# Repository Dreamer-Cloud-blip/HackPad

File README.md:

# SixPad

A compact, custom-designed screwless 6-key mechanical macropad built with a Seeeduino XIAO, a rotary encoder, a 128x32 OLED display, and powered by Python-based KMK firmware.

## Overall Macropad

## Schematic

## PCB Design

## Case & Assembly

## Bill of Materials (BOM)

- **Seeeduino XIAO:** 1x microcontroller
- **Mechanical Switches:** 6x switches
- **Rotary Encoder:** 1x encoder
- **OLED Display:** 1x 128x32 display
- **Case Parts:** 3D-printed top plate and bottom tray

## Repository Directory Structure

```text
├── CAD/
│   └── assembly.step
├── PCB/
│   ├── SixPad.kicad_pro
│   ├── SixPad.kicad_sch
│   └── SixPad.kicad_pcb
├── Firmware/
│   └── main.py
├── production/
│   ├── Top.STEP
│   ├── Bottom.STEP
│   ├── gerbers.zip
│   └── main.py
└── assets/
    ├── CAD.png
    ├── Schematic.png
    ├── PCB_layout.png
    └── case_assembly.png

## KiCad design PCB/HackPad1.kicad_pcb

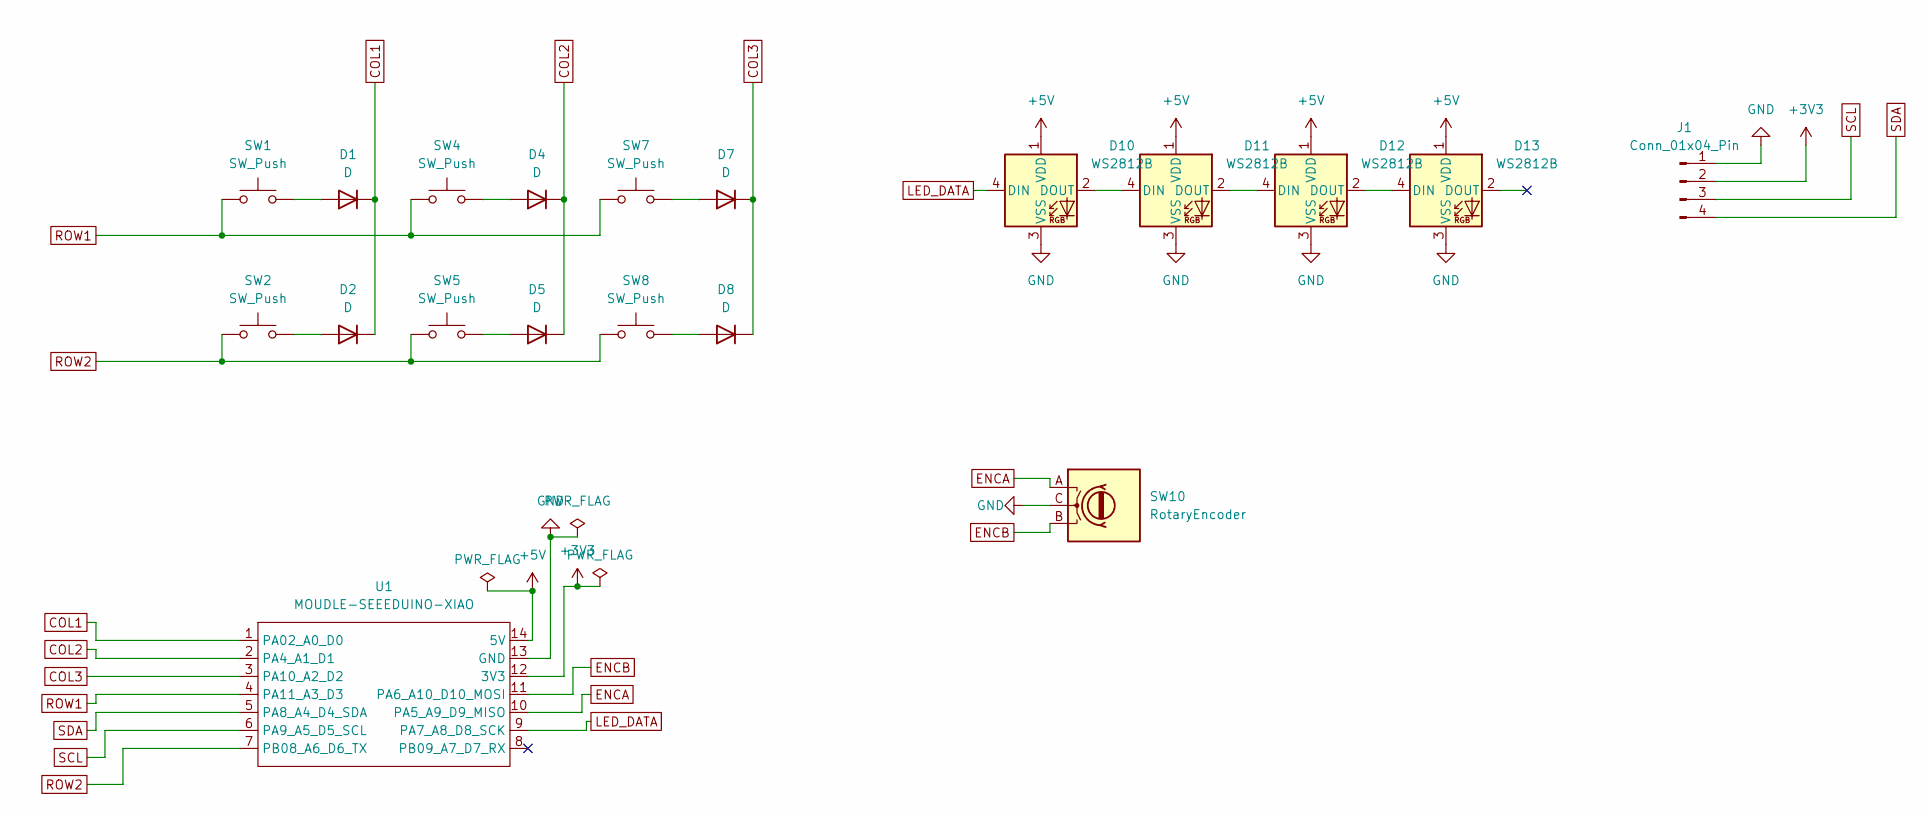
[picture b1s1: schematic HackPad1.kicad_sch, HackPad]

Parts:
D1, D2: D; D_DO-35_SOD27_P7.62mm_Horizontal
D4, D5, D7, D8: D; D_DO-35_SOD27_P10.16mm_Horizontal
D10, D11, D12, D13: WS2812B; LED_SK6812_PLCC4_5.0x5.0mm_P3.2mm
J1: Conn_01x04_Pin; PinSocket_1x04_P2.54mm_Vertical
SW1, SW2, SW4, SW5, SW7, SW8: SW_Push; SW_Cherry_MX_1.00u_PCB
SW10: RotaryEncoder; RotaryEncoder_Alps_EC11E-Switch_Vertical_H20mm
U1: MOUDLE-SEEEDUINO-XIAO; XIAO-SAMD21-DIP

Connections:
+3V3: J1.2, U1.12 (3V3)
+5V: D10.1 (VDD), D11.1 (VDD), D12.1 (VDD), D13.1 (VDD), U1.14 (5V)
COL1: D1.1 (K), D2.1 (K), U1.1 (PA02_A0_D0)
COL2: D4.1 (K), D5.1 (K), U1.2 (PA4_A1_D1)
COL3: D7.1 (K), D8.1 (K), U1.3 (PA10_A2_D2)
ENCA: SW10.A, U1.10 (PA5_A9_D9_MISO)
ENCB: SW10.B, U1.11 (PA6_A10_D10_MOSI)
GND: D10.3 (VSS), D11.3 (VSS), D12.3 (VSS), D13.3 (VSS), J1.1, SW10.C, U1.13 (GND)
LED_DATA: D10.4 (DIN), U1.9 (PA7_A8_D8_SCK)
unnamed: D1.2 (A), SW1.2
unnamed: D2.2 (A), SW2.2
unnamed: D4.2 (A), SW4.2
unnamed: D5.2 (A), SW5.2
unnamed: D7.2 (A), SW7.2
unnamed: D8.2 (A), SW8.2
unnamed: D10.2 (DOUT), D11.4 (DIN)
unnamed: D11.2 (DOUT), D12.4 (DIN)
unnamed: D12.2 (DOUT), D13.4 (DIN)
ROW1: SW1.1, SW4.1, SW7.1, U1.4 (PA11_A3_D3)
ROW2: SW2.1, SW5.1, SW8.1, U1.7 (PB08_A6_D6_TX)
SCL: J1.3, U1.6 (PA9_A5_D5_SCL)
SDA: J1.4, U1.5 (PA8_A4_D4_SDA)

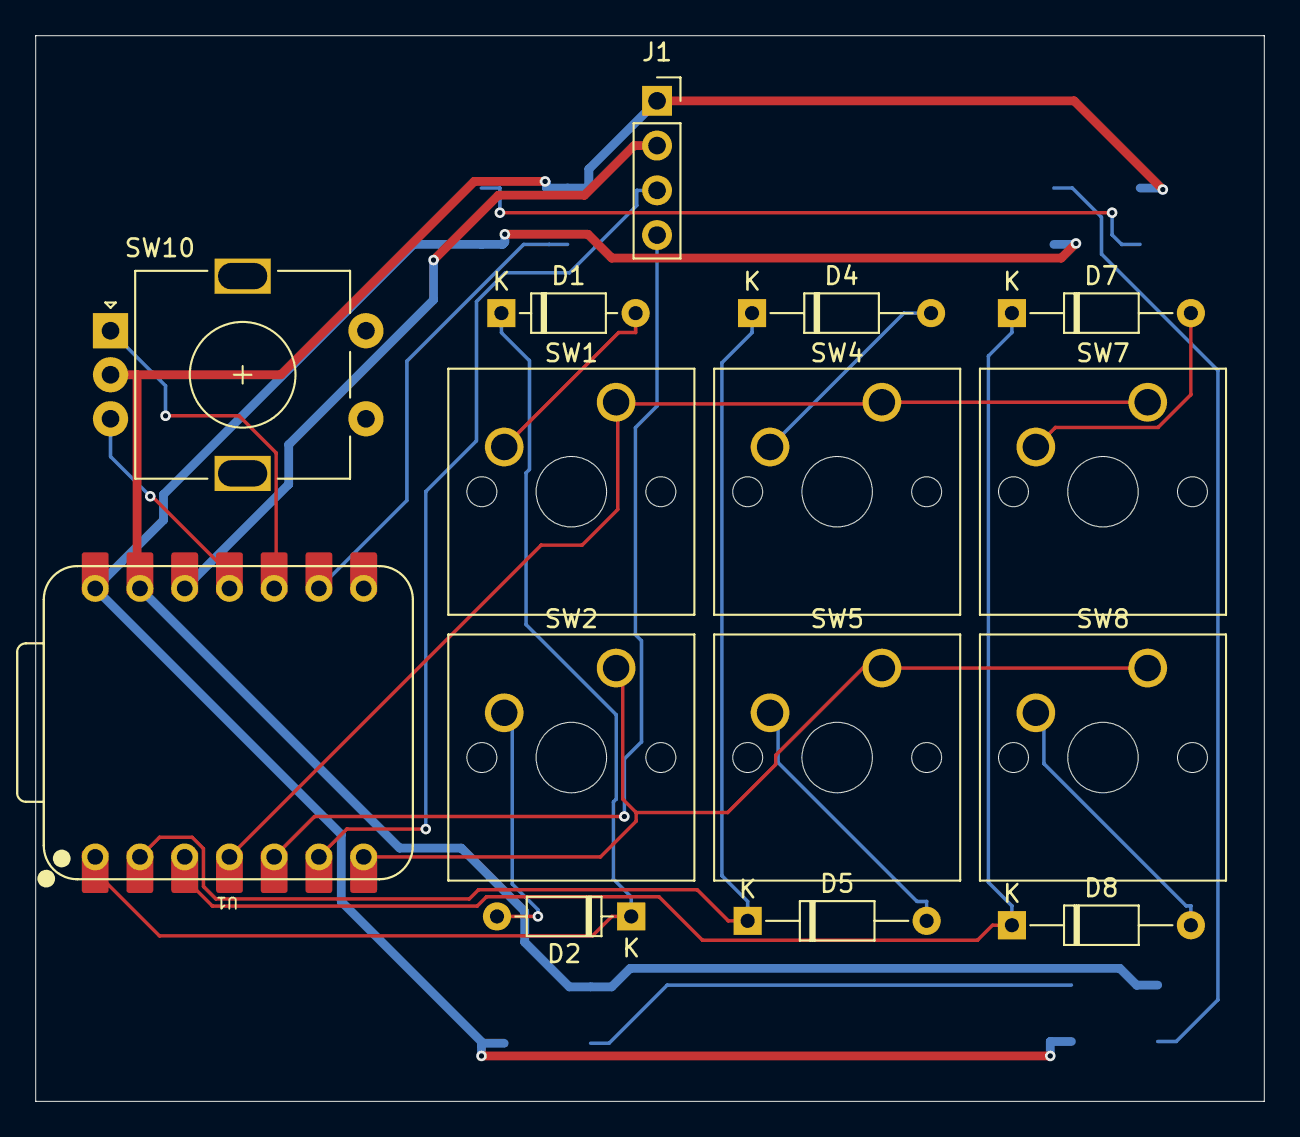
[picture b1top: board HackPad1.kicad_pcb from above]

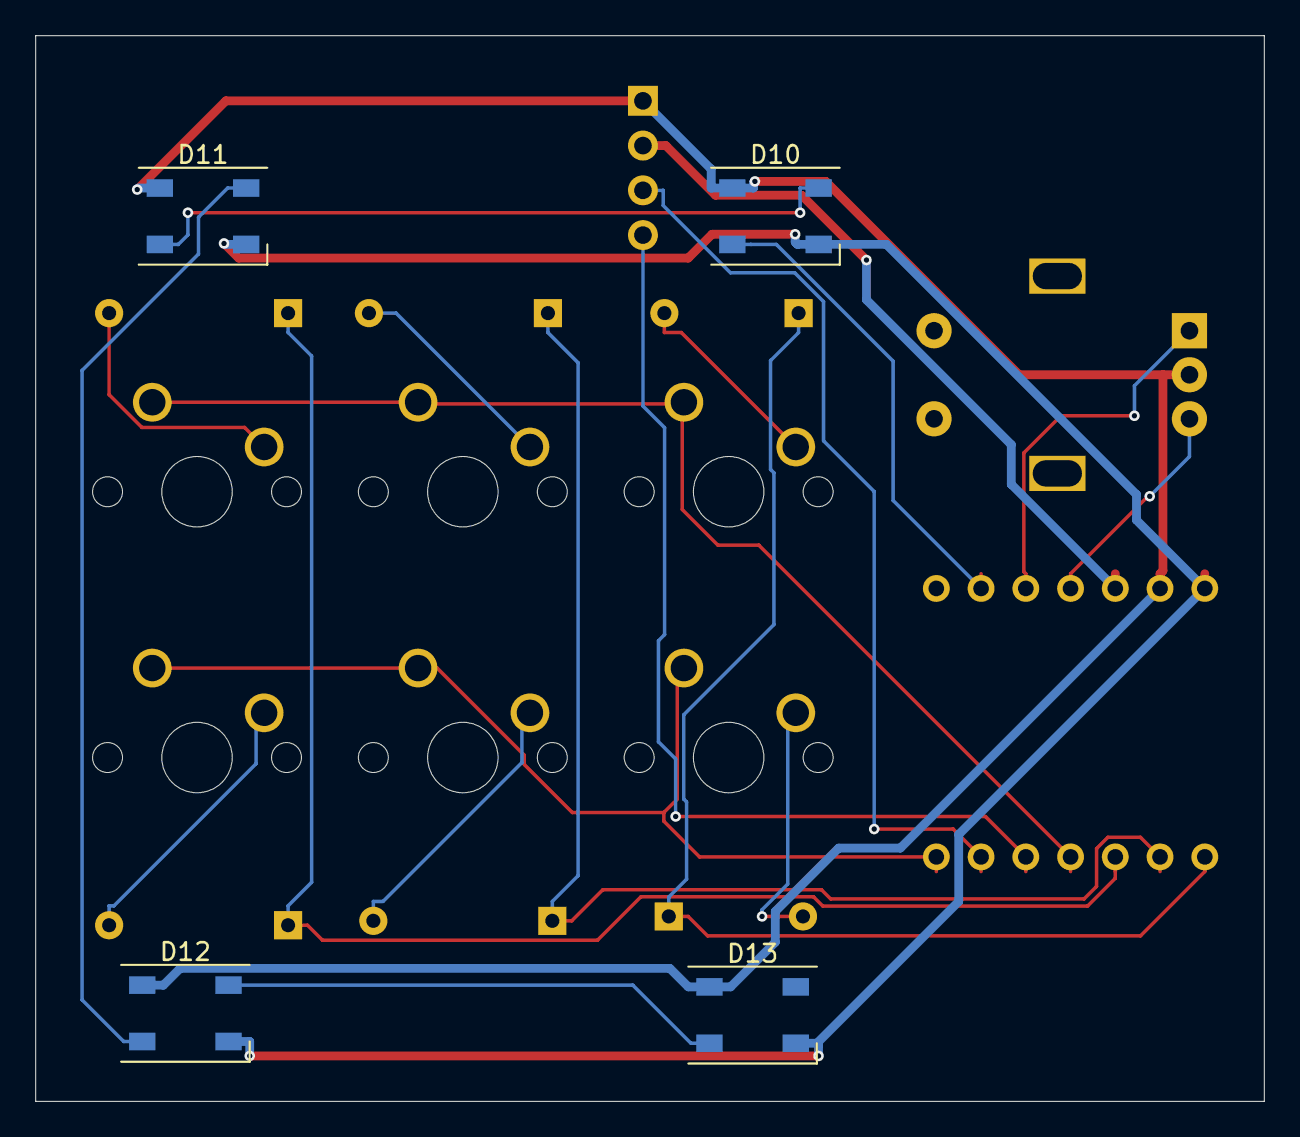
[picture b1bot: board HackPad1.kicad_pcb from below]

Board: 2 copper layers, 69.8 x 60.5 mm, 19 parts (4 on the bottom side), 22 nets.
